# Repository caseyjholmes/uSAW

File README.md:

# μSAW
TL074/Matched 3904/PSI powered SMD 2HP sized analog Voltage Controlled Saw Oscillator for Eurorack by Holmes Modular

View module on Modular Grid https://www.modulargrid.net/e/other-unknown-holmes-modular-%CE%BCsaw

This module is currently in the testing phase.

The BOM may also need an update. 

Panel and PCB have been tested 10/23/23. I'm testing BOM components and tuning now - Check back in a couple days will probably be done! 
-Casey

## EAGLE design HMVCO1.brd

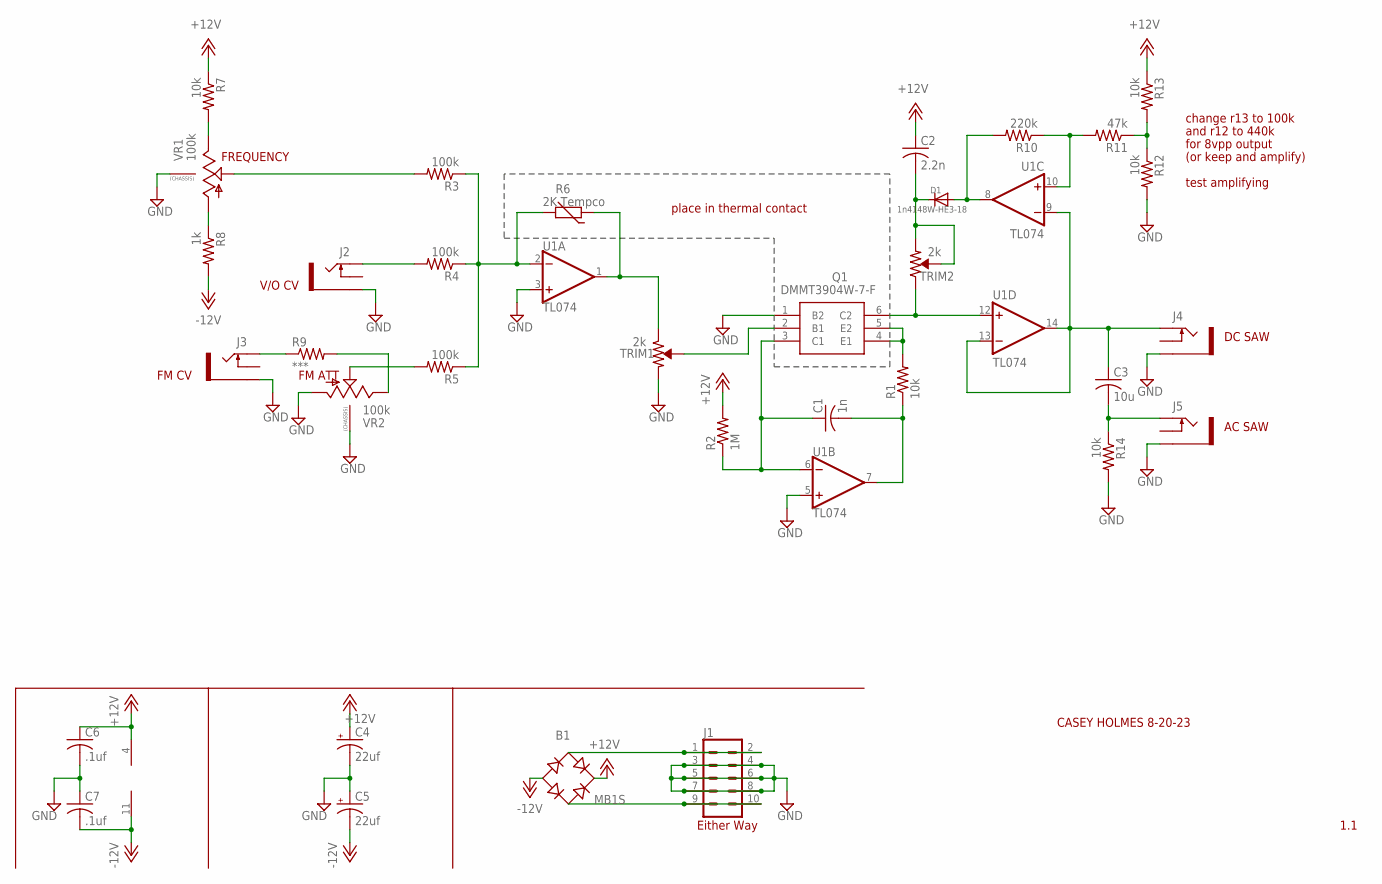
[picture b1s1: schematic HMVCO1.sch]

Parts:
B1: MB1S; SOIC-4
C1: 1n; C0603K
C2: 2.2n; C0603K
C3: 10u; C0603K
C4, C5: 22uf; PANASONIC_C
C6, C7: .1uf; C0603K
D1: 1n4148W-HE3-18; SOD-123
J1: CONN_05X2PTH; 2X5
J2, J3, J4, J5: THONKICONNNEW; WQP-PJ301M-12_JACK
Q1: DMMT3904W-7-F; SOT65P210X100-6N
R1, R7, R12, R13, R14: 10k; R0603
R2: 1M; R0603
R3, R4, R5: 100k; R0603
R6: 2K Tempco; R-5
R8: 1k; R0603
R9: ***; R0603
R10: 220k; R0603
R11: 47k; R0603
TRIM1, TRIM2: 2k; TRIMPOT-SMD-TC33X
U1: TL074; TSSOP14
VR1, VR2: 100k; 9MM_SNAP-IN_POT

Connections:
+12V: B1.+, C2.1, C4.+, C6.1, R2.2, R7.1, R13.1, U1.4 (V+)
-12V: B1.-, C5.-, C7.2, R8.2, U1.11 (V-)
GND: C4.-, C5.+, C6.2, C7.1, J1.3, J1.4, J1.5, J1.6, J1.7, J1.8, J2.P$3_SLEEVE (SLEEVE), J3.P$3_SLEEVE (SLEEVE), J4.P$3_SLEEVE (SLEEVE), J5.P$3_SLEEVE (SLEEVE), Q1.1 (B2), R12.2, R14.2, TRIM1.3 (CCW), U1.3 (+IN), U1.5 (+IN), VR1.CHASSIS1, VR1.CHASSIS2, VR2.1 (A), VR2.CHASSIS1, VR2.CHASSIS2
unnamed: Q1.4 (E1), Q1.5 (E2), R1.2
unnamed: Q1.2 (B1), TRIM1.2 (WIPER)
unnamed: Q1.6 (C2), TRIM2.1 (CW), U1.12 (+IN)
unnamed: R6.1, TRIM1.1 (CW), U1.1 (OUT)
unnamed: C1.1, Q1.3 (C1), R2.1, U1.6 (-IN)
unnamed: R3.1, R4.1, R5.1, R6.2, U1.2 (-IN)
unnamed: C1.2, R1.1, U1.7 (OUT)
unnamed: J2.P$1_TIP (TIP), R4.2
unnamed: R3.2, VR1.2 (S)
unnamed: R8.1, VR1.1 (A)
unnamed: R7.2, VR1.3 (E)
unnamed: R9.2, VR2.3 (E)
unnamed: R5.2, VR2.2 (S)
unnamed: J3.P$1_TIP (TIP), R9.1
unnamed: C3.1, J4.P$1_TIP (TIP), U1.9 (-IN), U1.13 (-IN), U1.14 (OUT)
unnamed: C2.2, D1.C, TRIM2.2 (WIPER), TRIM2.3 (CCW)
unnamed: D1.A, R10.2, U1.8 (OUT)
unnamed: R10.1, R11.2, U1.10 (+IN)
unnamed: R11.1, R12.1, R13.2
unnamed: C3.2, J5.P$1_TIP (TIP), R14.1
unnamed: B1.~2 (AC2), J1.9, J1.10
unnamed: B1.~1 (AC1), J1.1, J1.2

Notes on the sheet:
V/O CV
FM CV
FM ATT
FREQUENCY
place in thermal contact
DC SAW
AC SAW
Either Way
CASEY HOLMES 8-20-23
1.1
change r13 to 100k
and r12 to 440k
for 8vpp output
(or keep and amplify)
test amplifying

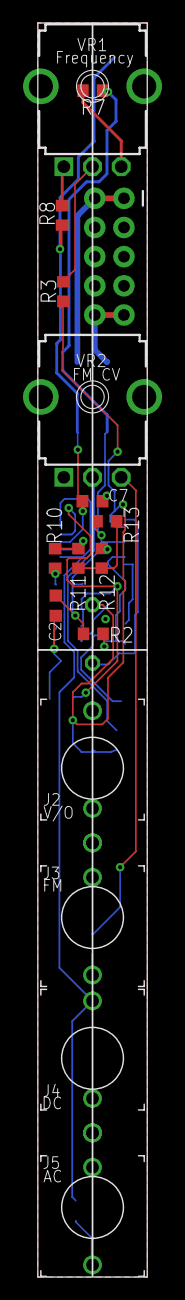
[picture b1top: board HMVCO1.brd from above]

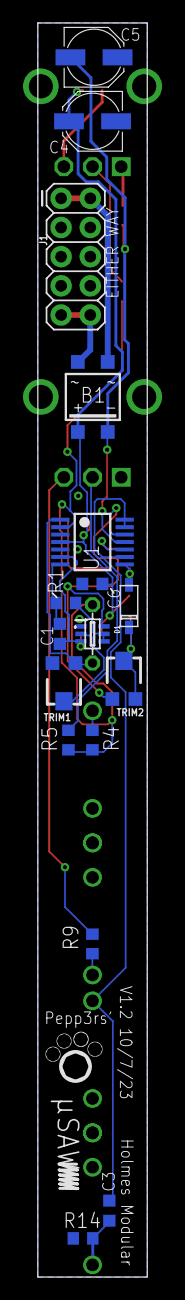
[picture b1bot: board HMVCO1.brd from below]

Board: 2 copper layers, 9.5 x 109.2 mm, 34 parts (18 on the bottom side), 25 nets.

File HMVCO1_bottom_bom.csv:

Comment,Designator,Footprint,LCSC Part #
***,R9,R0603,
.1uf,C6,C0603K,
1n,C1,C0603K,
1n4148W-HE3-18,D1,SOD-123,
2k,TRIM1 TRIM2,TRIMPOT-SMD-TC33X,
10k,R1 R14,R0603,
10u,C3,C0603K,
22uf,C4 C5,PANASONIC_C,
100k,R4 R5,R0603,
DMMT3904W-7-F,Q1,SOT65P210X100-6N,
MB1S,B1,SOIC-4,
TL074,U1,TSSOP14,

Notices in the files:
parts and their libraries:
SparkFun-Resistors: Licensing: Creative Commons ShareAlike 4.0 International - https://creativecommons.org/licenses/by-sa/4.0
